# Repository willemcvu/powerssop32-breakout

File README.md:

# powerssop32-breakout
A small PowerSSOP32 P0.65mm to DIP32 breakout board.

Available for sale here: https://www.tindie.com/products/willtronics/powerssop-32-p065mm-to-dip-32-breadboard-adapter/

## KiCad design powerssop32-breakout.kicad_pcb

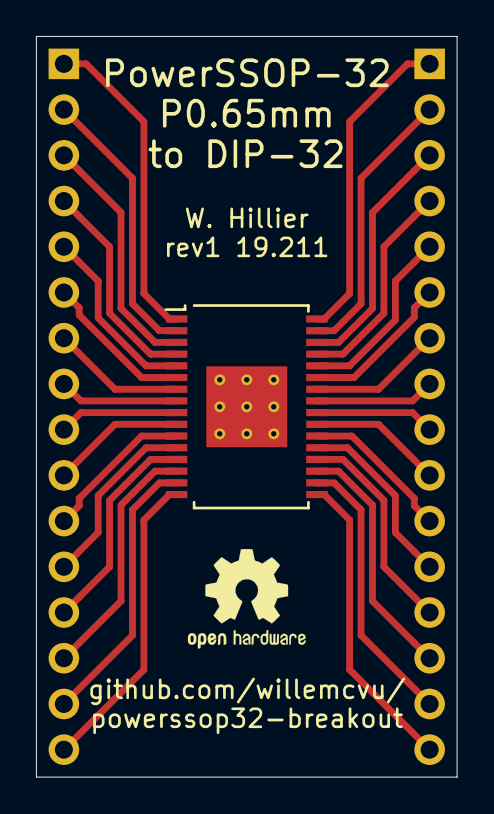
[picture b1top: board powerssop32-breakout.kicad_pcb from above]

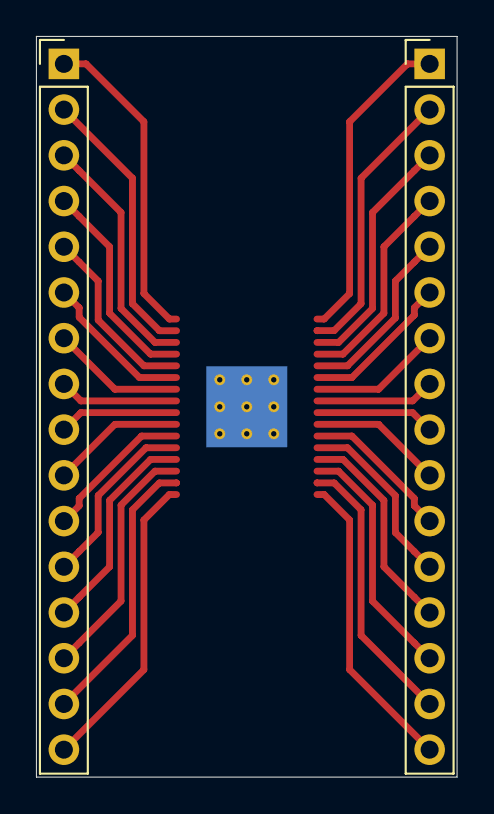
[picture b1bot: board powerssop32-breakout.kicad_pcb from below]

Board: 2 copper layers, 23.4 x 41.1 mm, 3 parts (2 on the bottom side), 32 nets.

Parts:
J1, J3: Conn_01x16; PinHeader_1x16_P2.54mm_Vertical
J2: Conn_02x16_Counter_Clockwise; PowerSSOP-32-1EP_6.5x11mm_P0.65mm_EP5.2x11mm_Mask4.11x4.36m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

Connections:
unnamed: J1.1, J2.1
unnamed: J1.2, J2.2
unnamed: J1.3, J2.3
unnamed: J1.4, J2.4
unnamed: J1.5, J2.5
unnamed: J1.6, J2.6
unnamed: J1.7, J2.7
unnamed: J1.8, J2.8
unnamed: J1.9, J2.9
unnamed: J1.10, J2.10
unnamed: J1.11, J2.11
unnamed: J1.12, J2.12
unnamed: J1.13, J2.13
unnamed: J1.14, J2.14
unnamed: J1.15, J2.15
unnamed: J1.16, J2.16
unnamed: J2.17, J3.16
unnamed: J2.18, J3.15
unnamed: J2.19, J3.14
unnamed: J2.20, J3.13
unnamed: J2.21, J3.12
unnamed: J2.22, J3.11
unnamed: J2.23, J3.10
unnamed: J2.24, J3.9
unnamed: J2.25, J3.8
unnamed: J2.26, J3.7
unnamed: J2.27, J3.6
unnamed: J2.28, J3.5
unnamed: J2.29, J3.4
unnamed: J2.30, J3.3
unnamed: J2.31, J3.2
unnamed: J2.32, J3.1
